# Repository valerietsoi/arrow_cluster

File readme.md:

# arrow cluster

extremely good for navigating spectra or arrowkeyless keyboards

<br>

## pics
| | |
| --- | --- |
|   |  |

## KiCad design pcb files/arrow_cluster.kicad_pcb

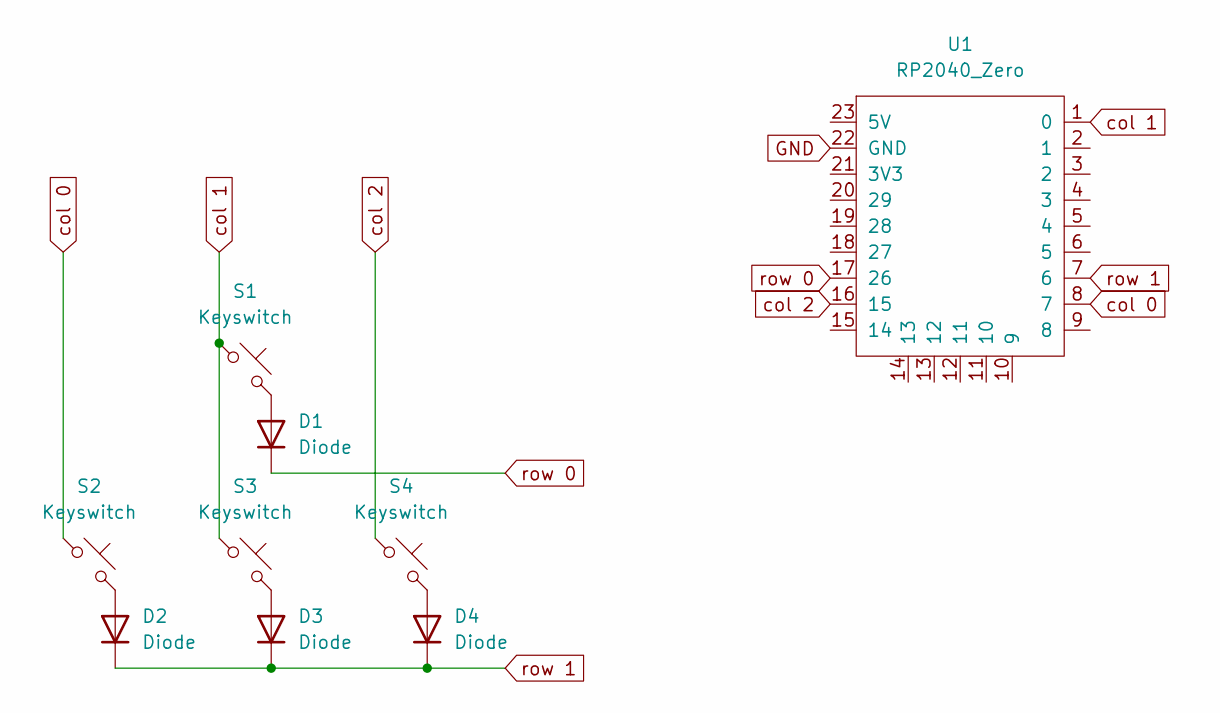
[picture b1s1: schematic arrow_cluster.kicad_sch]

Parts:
D1, D2, D3, D4: Diode; Diode_SOD-123
S1, S2, S3, S4: Keyswitch; MX_PCB_1.00u
U1: RP2040_Zero

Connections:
GND: U1.22 (GND)
unnamed: D1.2 (A), S1.2
unnamed: D2.2 (A), S2.2
unnamed: D3.2 (A), S3.2
unnamed: D4.2 (A), S4.2
col 0: S2.1, U1.8 (7)
col 1: S1.1, S3.1, U1.1 (0)
col 2: S4.1, U1.16 (15)
row 0: D1.1 (K), U1.17 (26)
row 1: D2.1 (K), D3.1 (K), D4.1 (K), U1.7 (6)

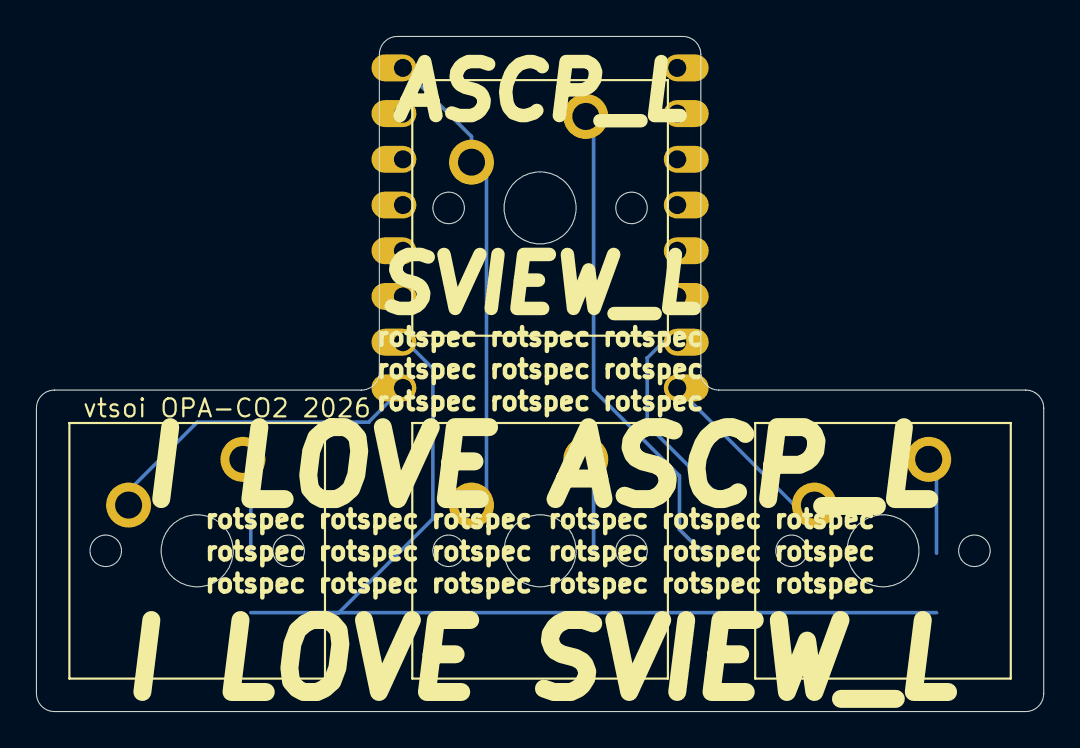
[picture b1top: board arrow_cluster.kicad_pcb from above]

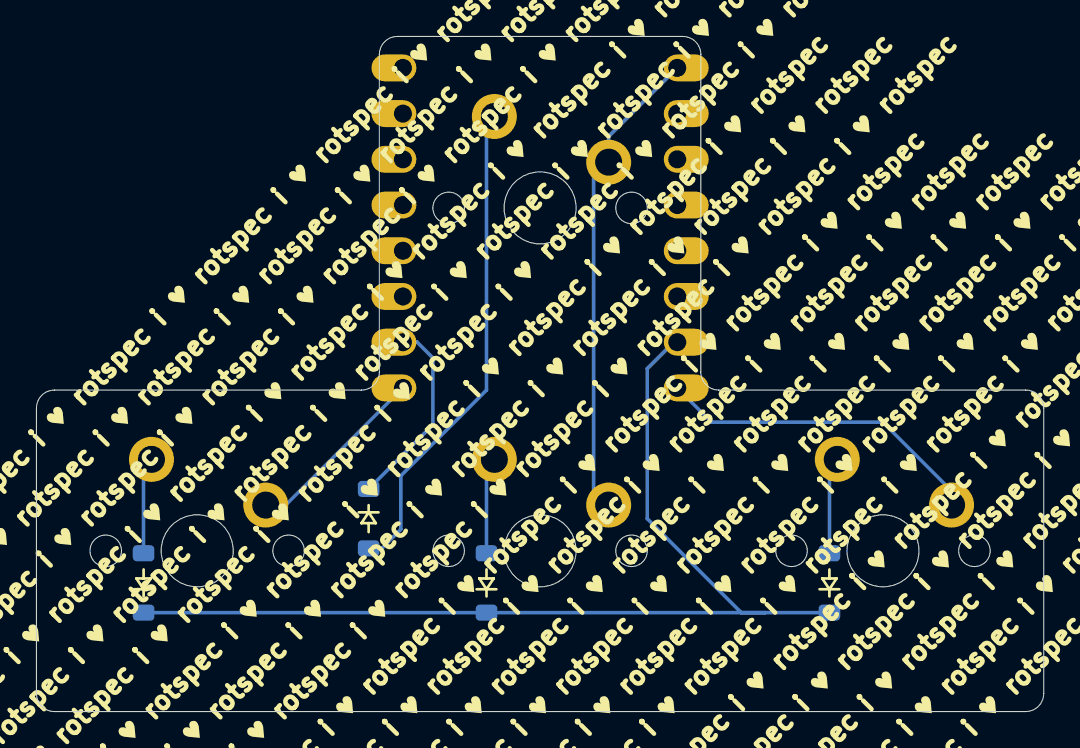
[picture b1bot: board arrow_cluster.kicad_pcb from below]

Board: 2 copper layers, 56.0 x 37.5 mm, 9 parts (5 on the bottom side), 9 nets.

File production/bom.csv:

Designator,Footprint,Quantity,Value,LCSC Part #
"D1, D2, D3, D4",Diode_SOD-123,4,Diode,
"S1, S2, S3, S4",MX_PCB_1.00u,4,Keyswitch,
U1,RP2040_Zero,1,RP2040_Zero,

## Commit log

2026-04-22 files
2026-04-22 reorganisation
2026-04-22 readme added
2026-04-22 duplicate removed
